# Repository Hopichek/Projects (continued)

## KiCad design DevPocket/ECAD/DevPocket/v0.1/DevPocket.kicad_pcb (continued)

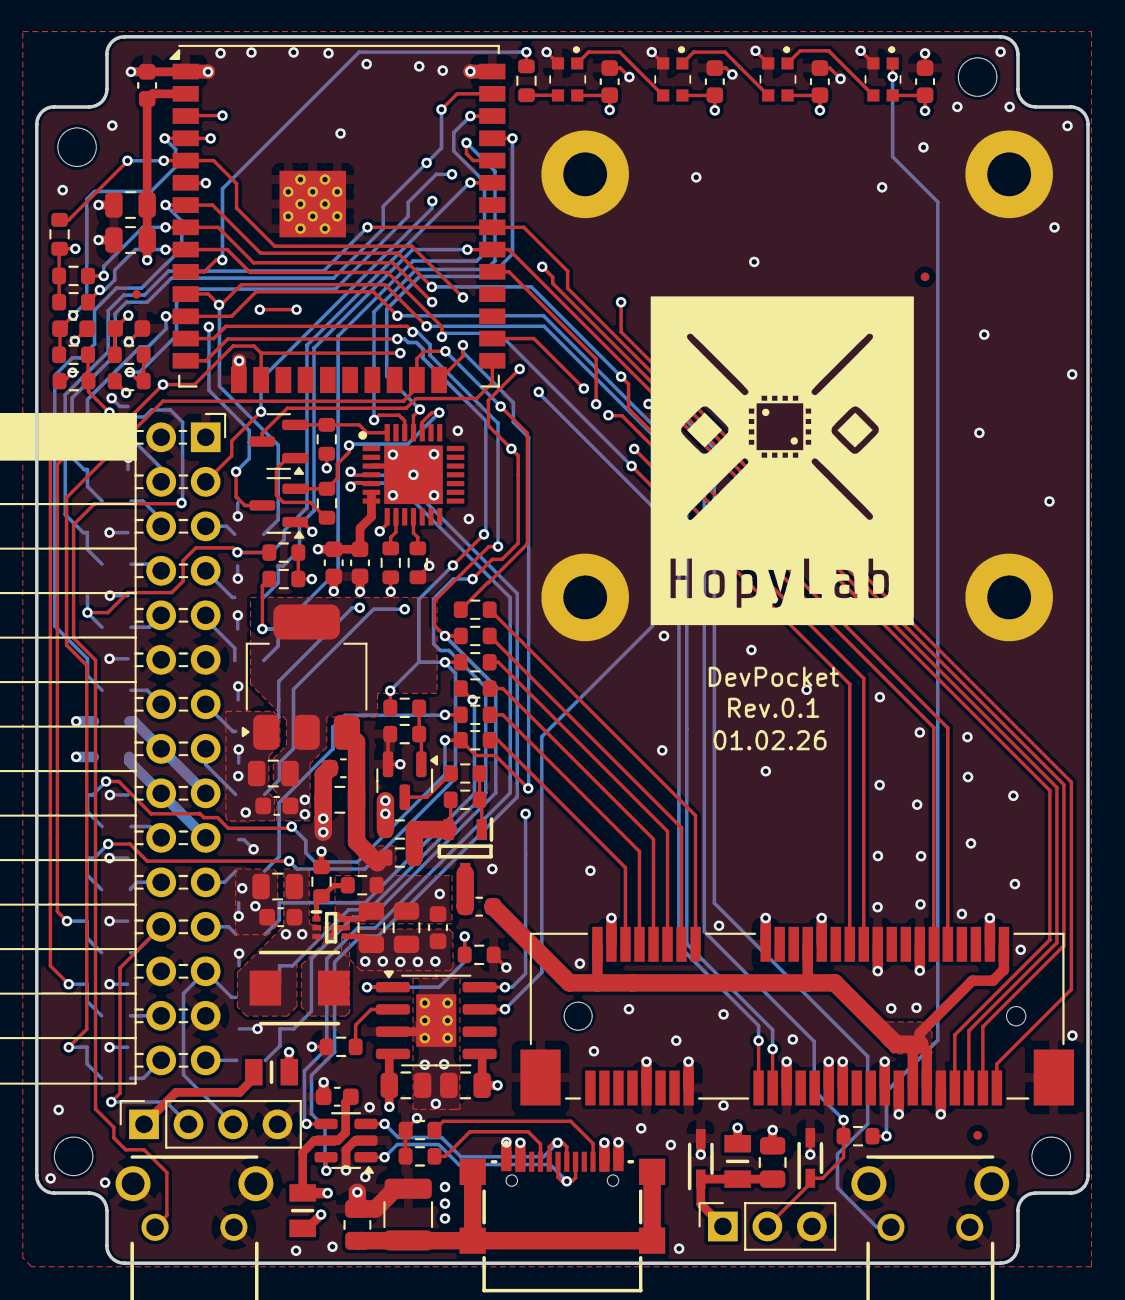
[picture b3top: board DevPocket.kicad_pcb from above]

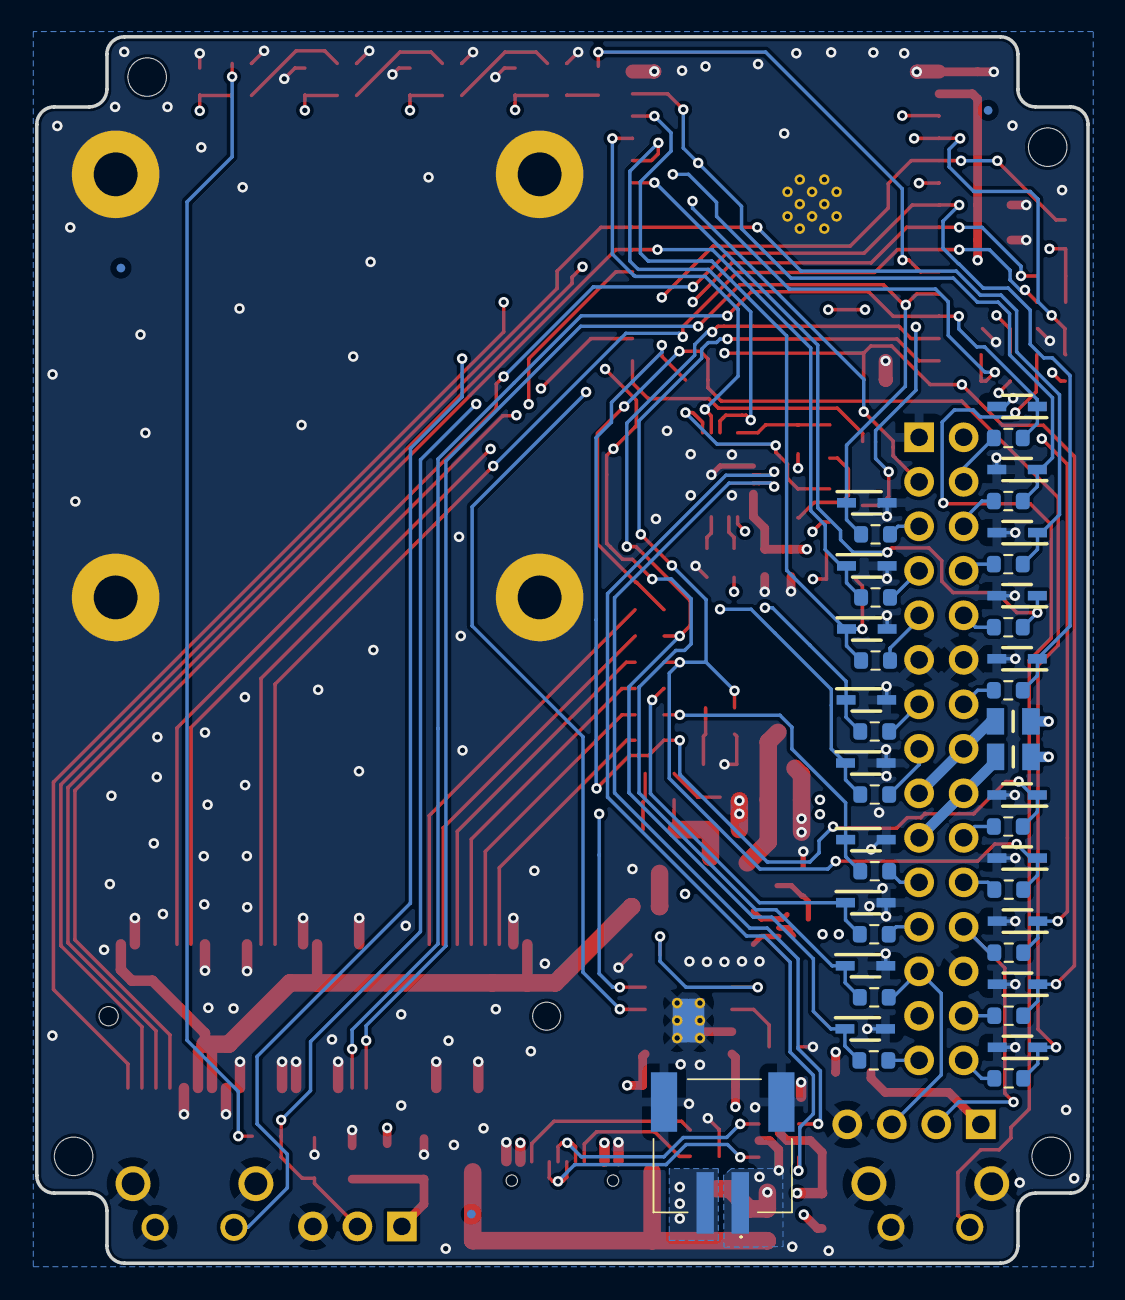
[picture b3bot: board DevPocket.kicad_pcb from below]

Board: 4 copper layers, 60.0 x 70.0 mm, 142 parts (44 on the bottom side), 91 nets.

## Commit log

2018-05-29 critter
2018-05-29 strings
2018-05-30 Add files via upload
    Streeams
2026-03-29 Adding a project
2026-05-06 Adding Mechanics files
